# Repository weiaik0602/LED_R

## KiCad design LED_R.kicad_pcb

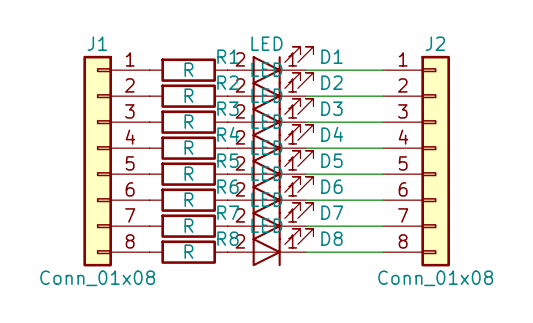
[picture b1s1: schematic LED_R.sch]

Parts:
D1, D2, D3, D4, D5, D6, D7, D8: LED; LED_0805
J1, J2: Conn_01x08; Pin_Header_Straight_1x08_Pitch2.54mm
R1, R2, R3, R4, R5, R6, R7, R8: R; R_0603

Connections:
unnamed: D1.1 (K), J2.1
unnamed: D1.2 (A), R1.1
unnamed: D2.1 (K), J2.2
unnamed: D2.2 (A), R2.1
unnamed: D3.1 (K), J2.3
unnamed: D3.2 (A), R3.1
unnamed: D4.1 (K), J2.4
unnamed: D4.2 (A), R4.1
unnamed: D5.1 (K), J2.5
unnamed: D5.2 (A), R5.1
unnamed: D6.1 (K), J2.6
unnamed: D6.2 (A), R6.1
unnamed: D7.1 (K), J2.7
unnamed: D7.2 (A), R7.1
unnamed: D8.1 (K), J2.8
unnamed: D8.2 (A), R8.1
unnamed: J1.1, R1.2
unnamed: J1.2, R2.2
unnamed: J1.3, R3.2
unnamed: J1.4, R4.2
unnamed: J1.5, R5.2
unnamed: J1.6, R6.2
unnamed: J1.7, R7.2
unnamed: J1.8, R8.2

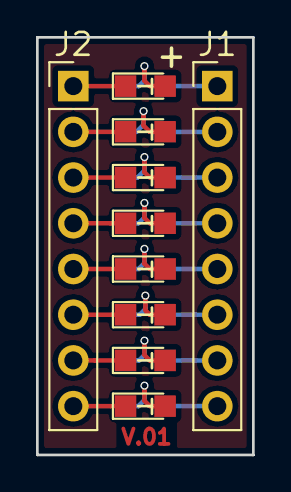
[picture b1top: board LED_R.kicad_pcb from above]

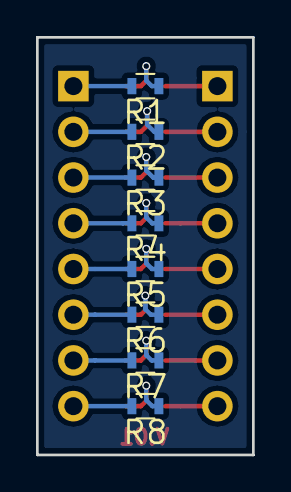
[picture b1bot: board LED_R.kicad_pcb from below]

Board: 2 copper layers, 12.0 x 23.2 mm, 18 parts (8 on the bottom side), 24 nets.

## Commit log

2017-11-14 created project and done
2017-11-15 added size,gerber file and drill hole
2017-11-29 changed the text size and position
